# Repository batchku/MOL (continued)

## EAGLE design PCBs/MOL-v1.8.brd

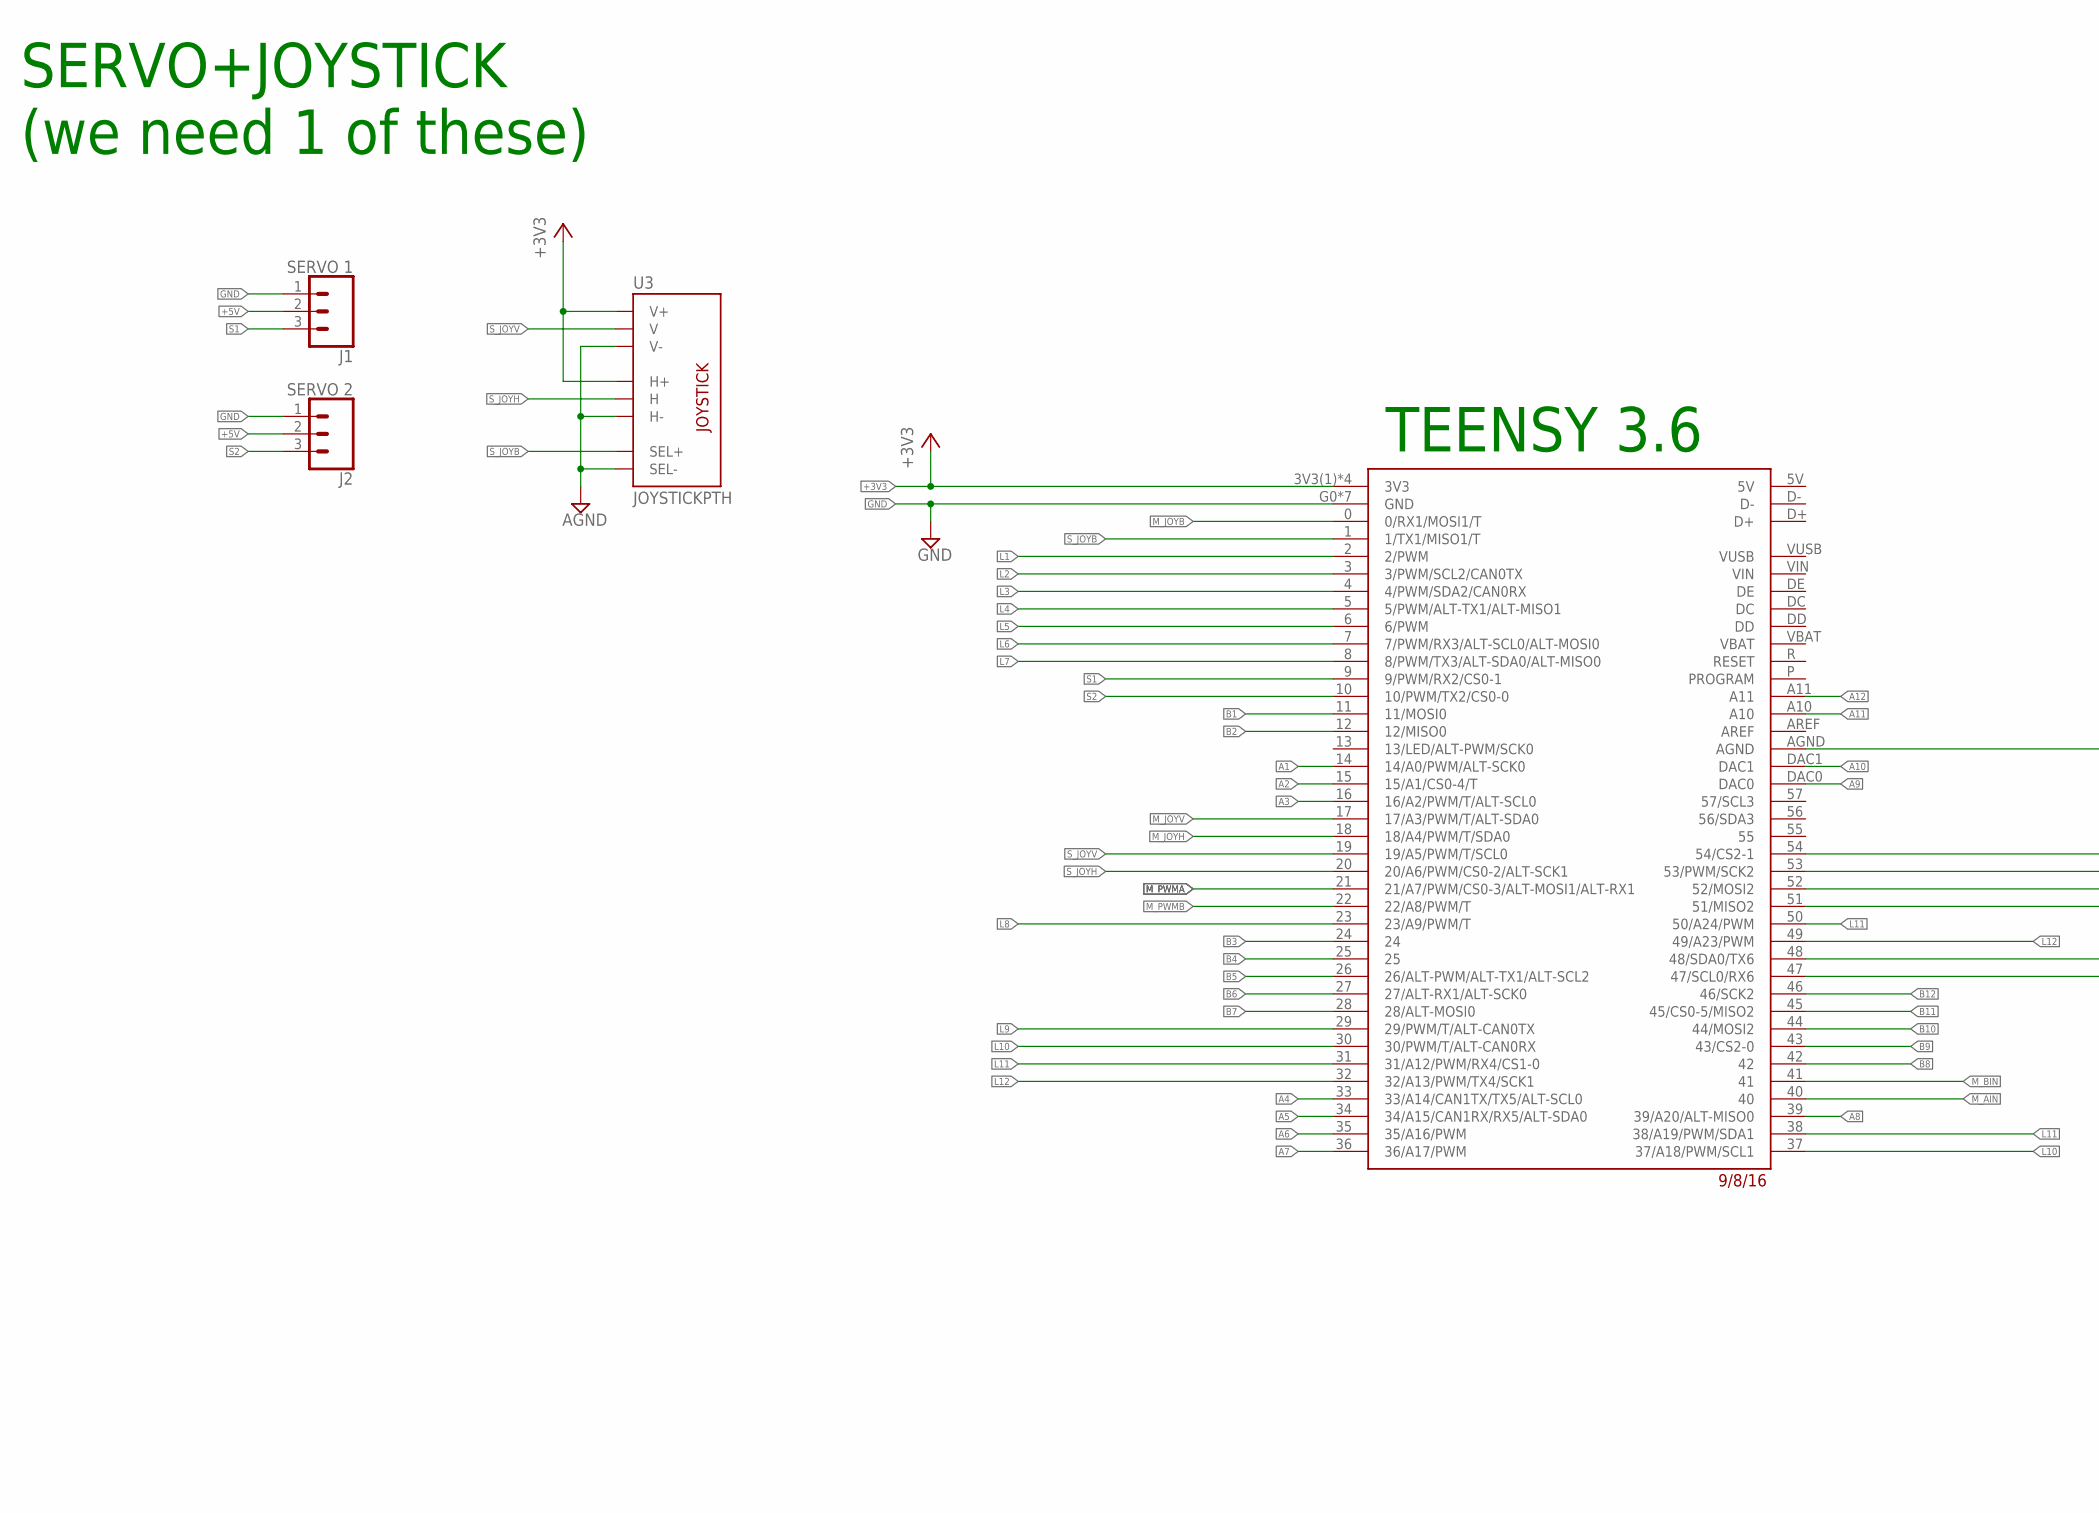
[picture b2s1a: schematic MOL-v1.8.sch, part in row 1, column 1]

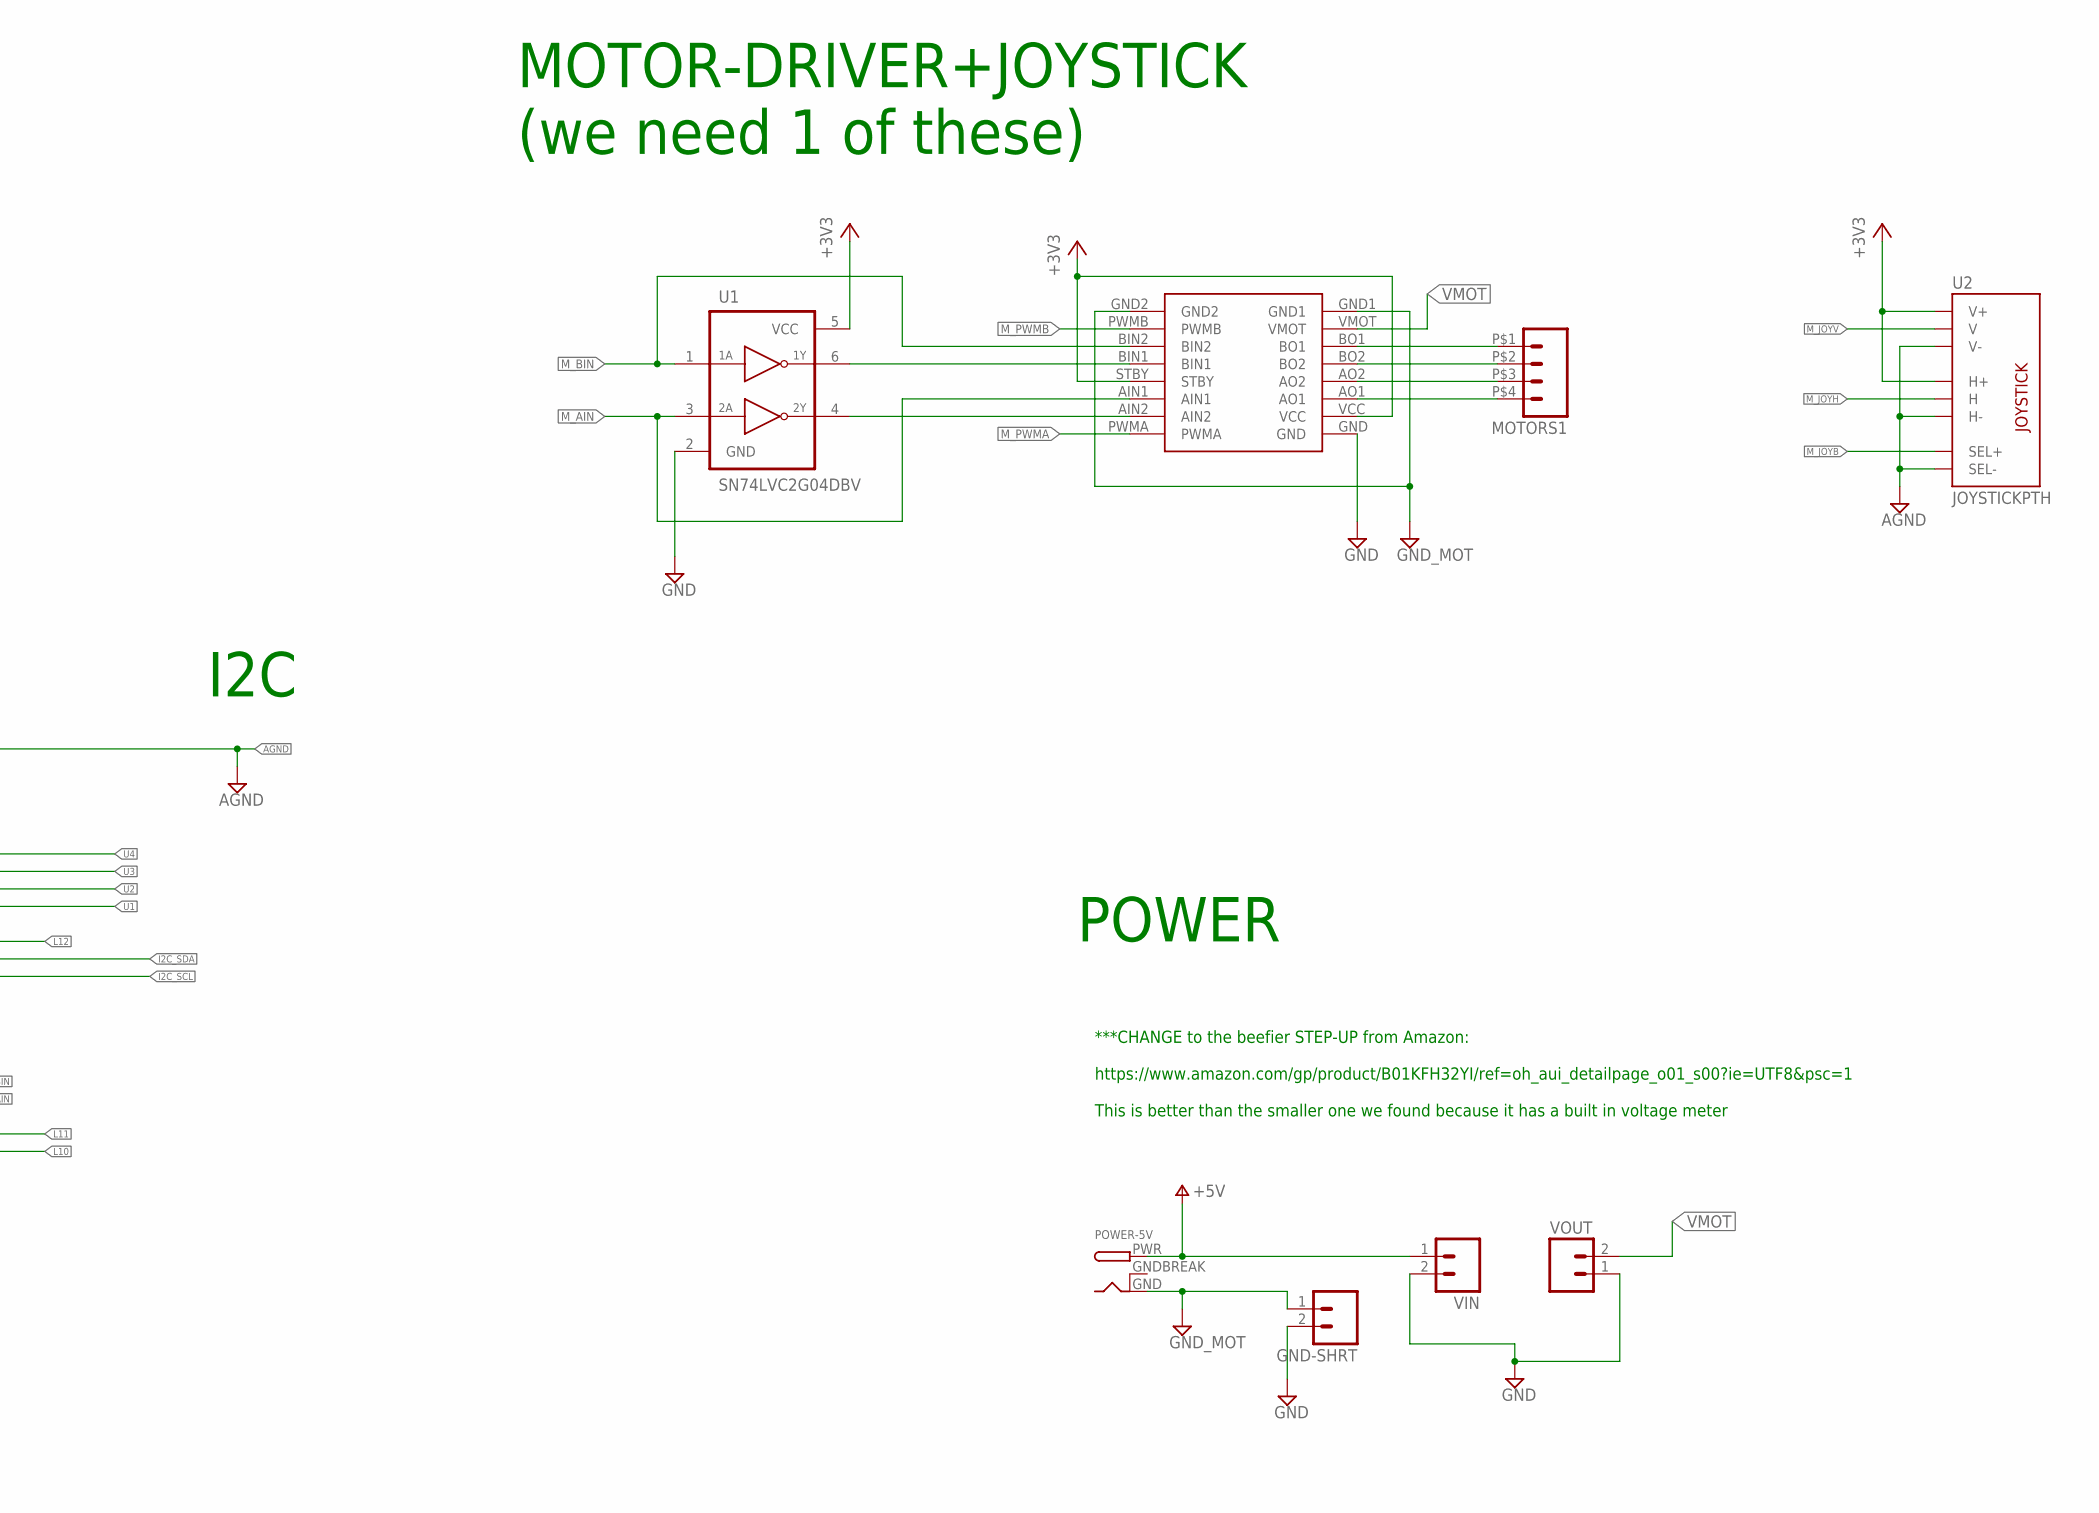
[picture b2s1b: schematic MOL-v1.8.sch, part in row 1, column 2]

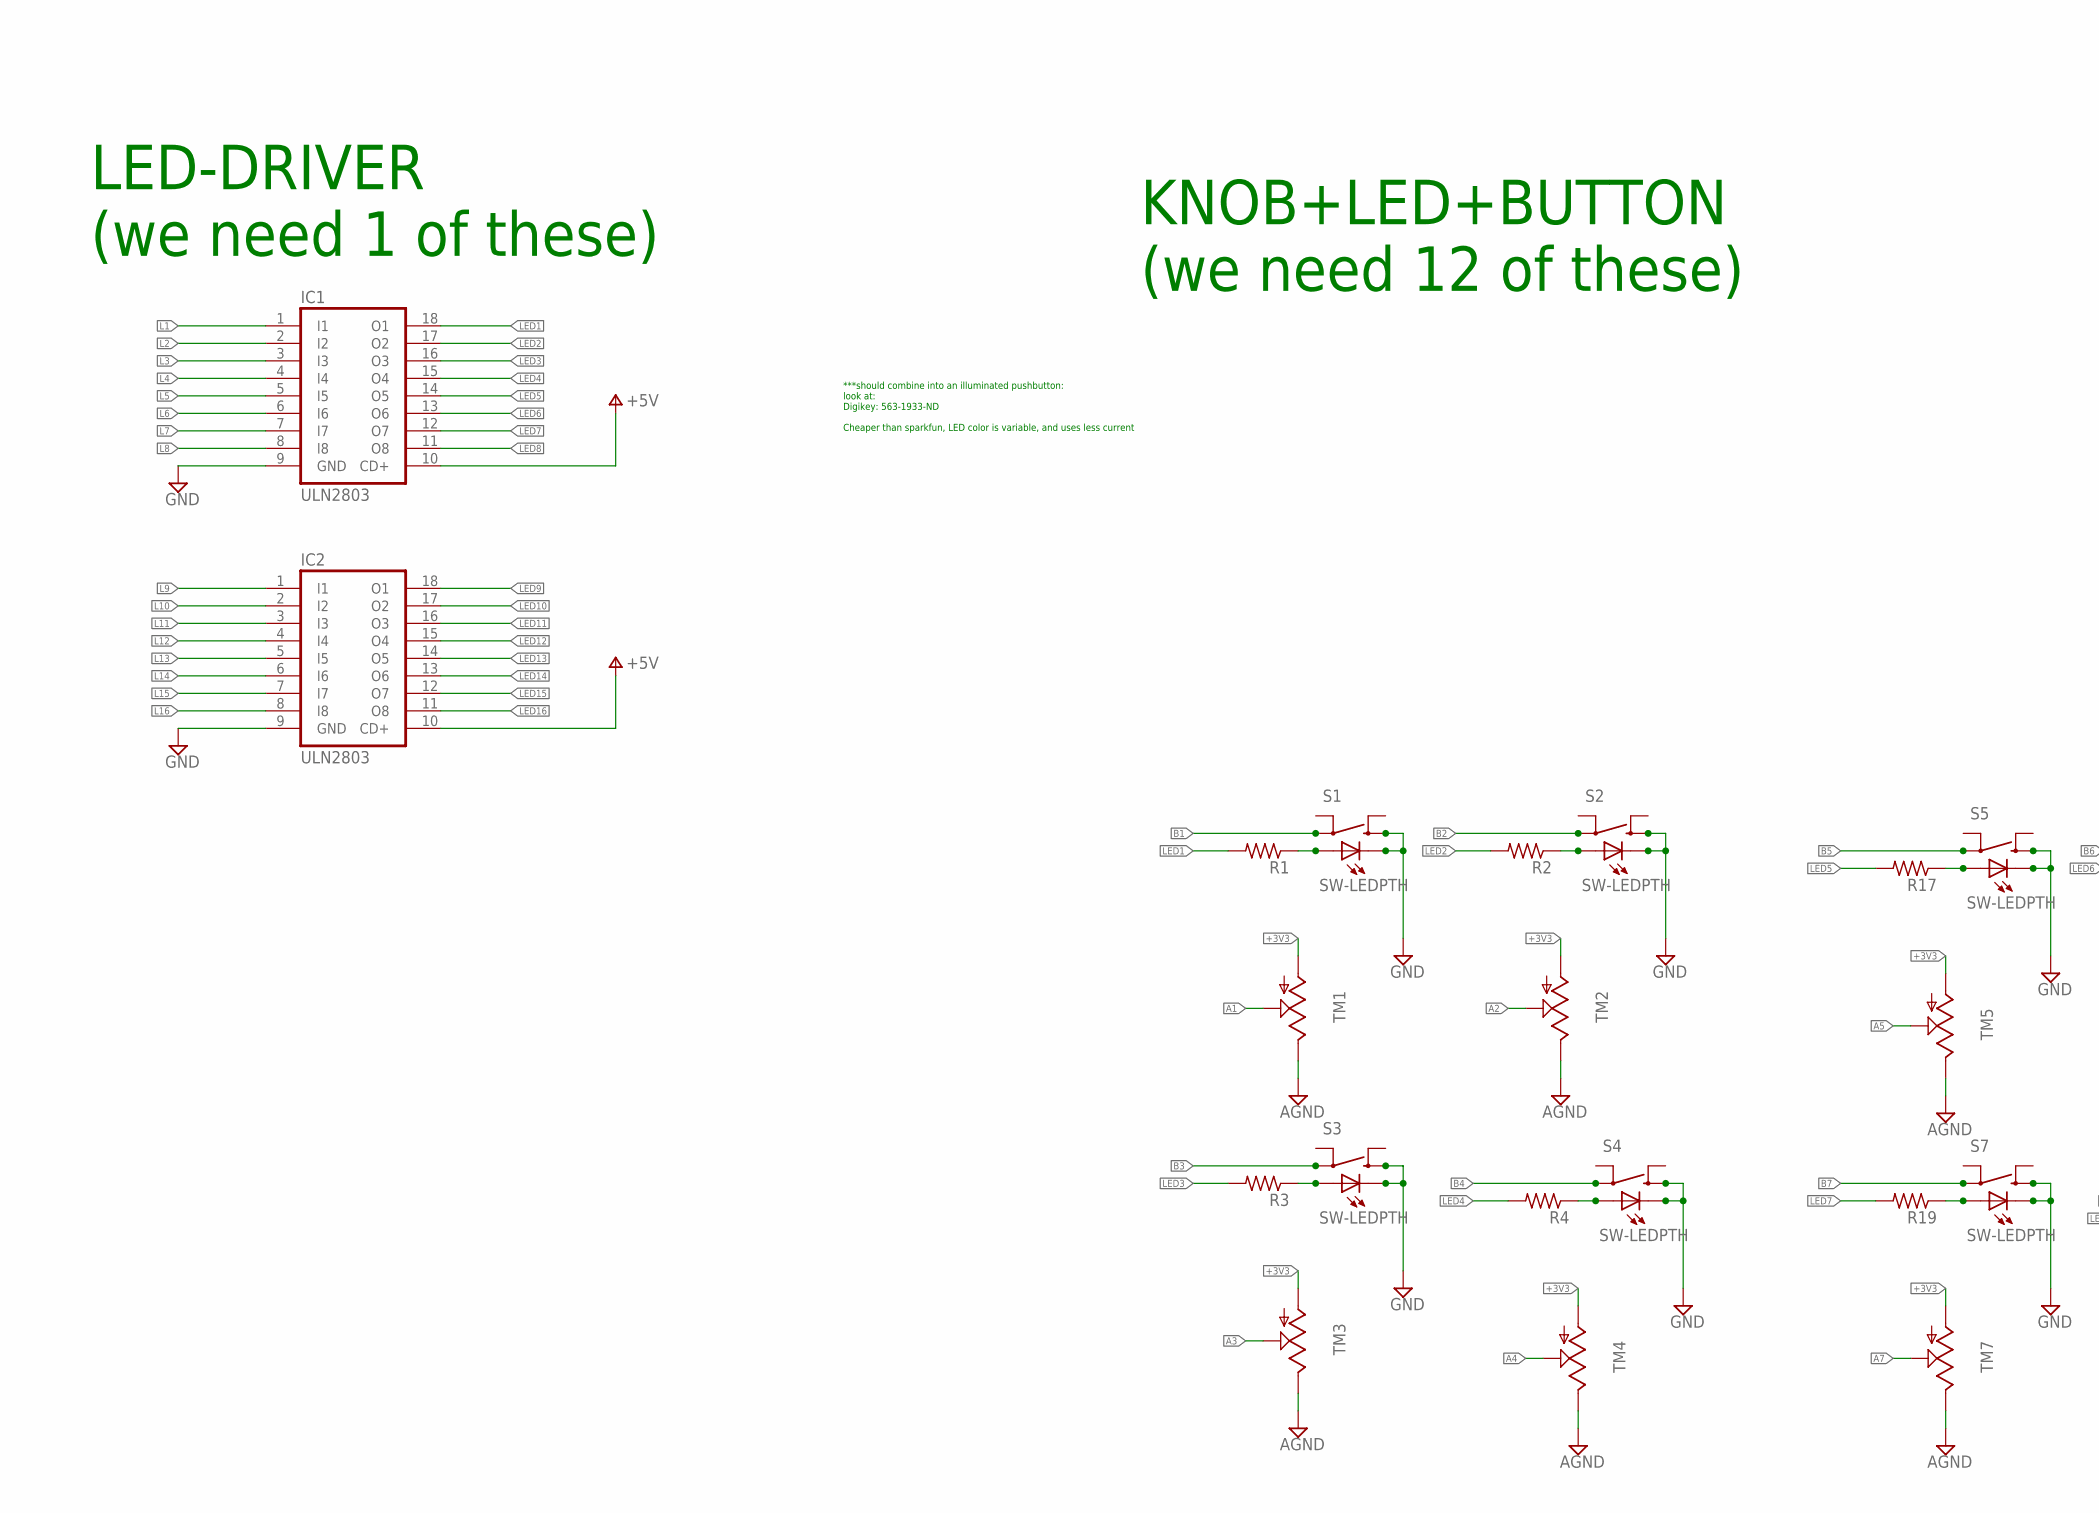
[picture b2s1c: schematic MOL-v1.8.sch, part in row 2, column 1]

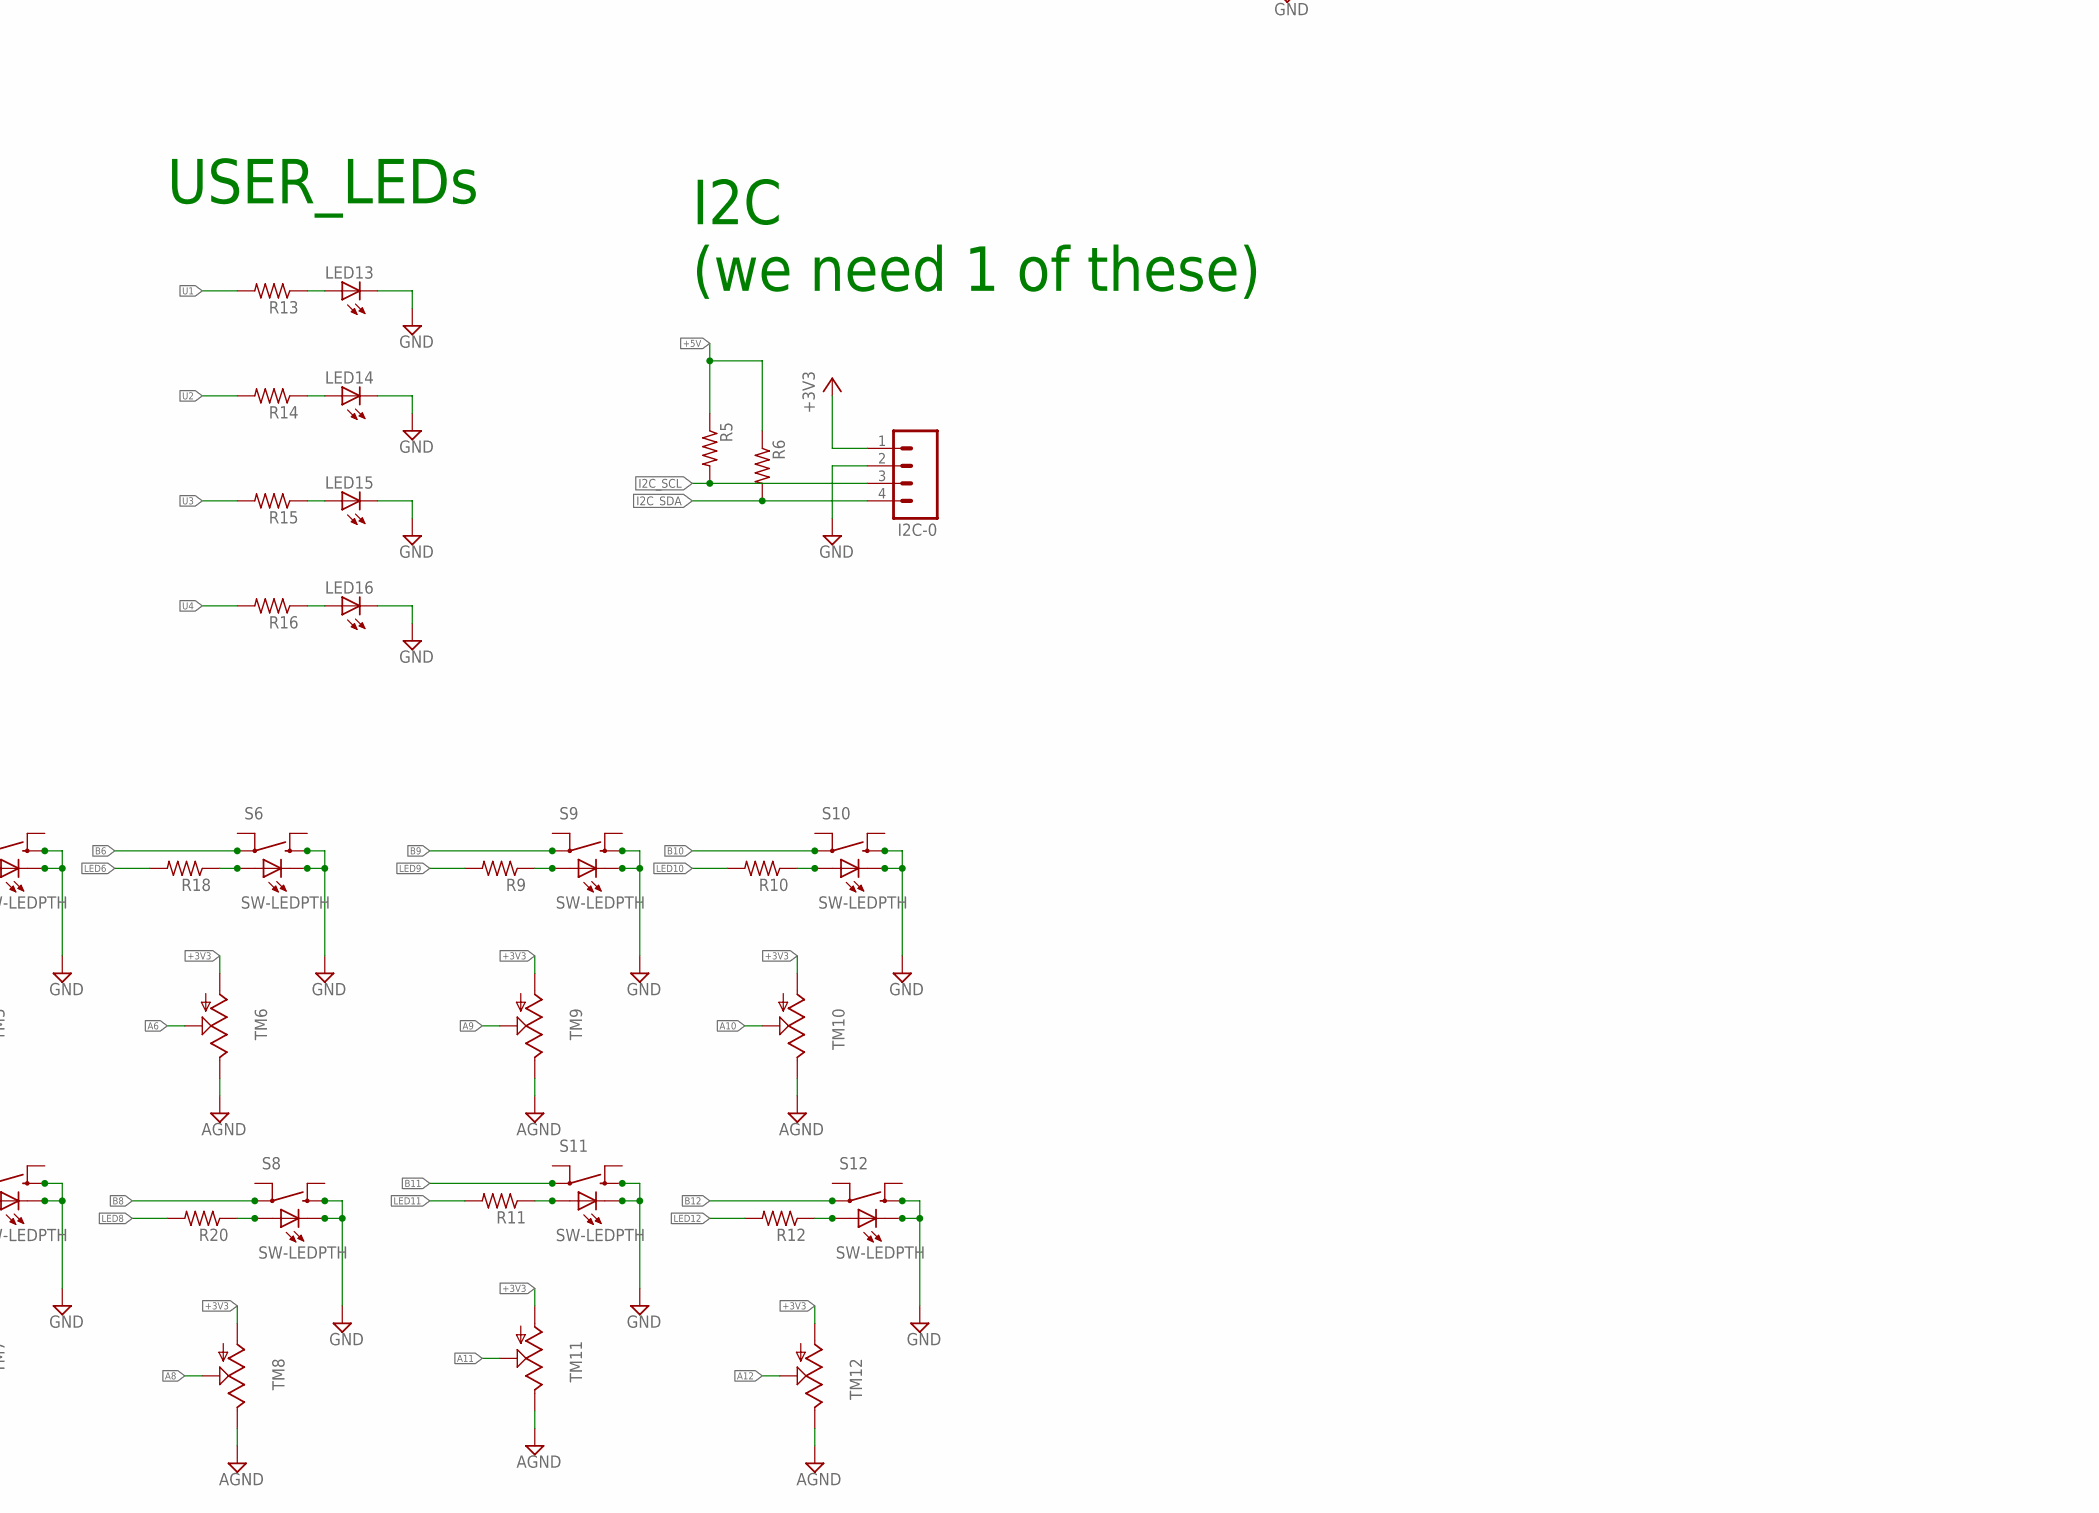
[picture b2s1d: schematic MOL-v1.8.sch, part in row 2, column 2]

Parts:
GND-SHRT: M02LOCK; 1X02_LOCK
I2C-0: M04LOCK; 1X04_LOCK
IC1, IC2: ULN2803; DIL18
J1: SERVO 1; 1X03_LOCK
J2: SERVO 2; 1X03_LOCK
LED13, LED14, LED15, LED16: LED3MM
MOTORS1: M04; SPRINGTERMINAL-2.54MM-4
POWER-5V: DCBARRELPTH; DCJACK_2MM_PTH
R1, R2, R3, R4, R5, R6, R9, R10, R11, R12, R13, R14, R15, R16, R17, R18, R19, R20: R-US_R0603; R0603
S1, S2, S3, S4, S5, S6, S7, S8, S9, S10, S11, S12: SW-LEDPTH; TR2-SWITCH-MOMENTARY-LED
TM1, TM2, TM3, TM4, TM5, TM6, TM7, TM8, TM9, TM10, TM11, TM12: TRIM; TRIM-PCB-9MM
U1: SN74LVC2G04DBV; SOT23-6
U2, U3: JOYSTICKPTH; JOYSTICK
U$1: TEENSY3_6--ALLPINS; T36
U$7: POLOLU_TB6612FNG
VIN: M02LOCK; 1X02_LOCK
VOUT: M02LOCK; 1X02_LOCK

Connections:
+3V3: I2C-0.1, TM1.1 (A), TM2.1 (A), TM3.1 (A), TM4.1 (A), TM5.1 (A), TM6.1 (A), TM7.1 (A), TM8.1 (A), TM9.1 (A), TM10.1 (A), TM11.1 (A), TM12.1 (A), U1.5 (VCC), U2.H1 (H+), U2.V1 (V+), U3.H1 (H+), U3.V1 (V+), U$1.3V3(1) (3V3), U$1.3V3(2) (3V3), U$1.3V3(3) (3V3), U$1.3V3(4) (3V3), U$7.STBY, U$7.VCC
+5V: IC1.10 (CD+), IC2.10 (CD+), J1.2, J2.2, POWER-5V.PWR, R5.1, R6.1, VIN.1
A1: TM1.2 (S), U$1.14 (14/A0/PWM/ALT-SCK0)
A2: TM2.2 (S), U$1.15 (15/A1/CS0-4/T)
A3: TM3.2 (S), U$1.16 (16/A2/PWM/T/ALT-SCL0)
A4: TM4.2 (S), U$1.33 (33/A14/CAN1TX/TX5/ALT-SCL0)
A5: TM5.2 (S), U$1.34 (34/A15/CAN1RX/RX5/ALT-SDA0)
A6: TM6.2 (S), U$1.35 (35/A16/PWM)
A7: TM7.2 (S), U$1.36 (36/A17/PWM)
A8: TM8.2 (S), U$1.39 (39/A20/ALT-MISO0)
A9: TM9.2 (S), U$1.DAC0
A10: TM10.2 (S), U$1.DAC1
A11: TM11.2 (S), U$1.A10
A12: TM12.2 (S), U$1.A11
AGND: TM1.3 (E), TM2.3 (E), TM3.3 (E), TM4.3 (E), TM5.3 (E), TM6.3 (E), TM7.3 (E), TM8.3 (E), TM9.3 (E), TM10.3 (E), TM11.3 (E), TM12.3 (E), U2.B2A (SEL-), U2.H3 (H-), U2.V3 (V-), U3.B2A (SEL-), U3.H3 (H-), U3.V3 (V-), U$1.AGND
B1: S1.3, U$1.11 (11/MOSI0)
B2: S2.3, U$1.12 (12/MISO0)
B3: S3.3, U$1.24
B4: S4.3, U$1.25
B5: S5.3, U$1.26 (26/ALT-PWM/ALT-TX1/ALT-SCL2)
B6: S6.3, U$1.27 (27/ALT-RX1/ALT-SCK0)
B7: S7.3, U$1.28 (28/ALT-MOSI0)
B8: S8.3, U$1.42
B9: S9.3, U$1.43 (43/CS2-0)
B10: S10.3, U$1.44 (44/MOSI2)
B11: S11.3, U$1.45 (45/CS0-5/MISO2)
B12: S12.3, U$1.46 (46/SCK2)
GND: GND-SHRT.2, I2C-0.2, IC1.9 (GND), IC2.9 (GND), J1.1, J2.1, LED13.K (C), LED14.K (C), LED15.K (C), LED16.K (C), S1.1, S1.C, S2.1, S2.C, S3.1, S3.C, S4.1, S4.C, S5.1, S5.C, S6.1, S6.C, S7.1, S7.C, S8.1, S8.C, S9.1, S9.C, S10.1, S10.C, S11.1, S11.C, S12.1, S12.C, U1.2 (GND), U$1.G0 (GND), U$1.G1 (GND), U$1.G2 (GND), U$1.G3 (GND), U$1.G4 (GND), U$1.G5 (GND), U$1.G6 (GND), U$7.GND, VIN.2, VOUT.1
GNDBREAK: POWER-5V.GNDBREAK
GND_MOT: GND-SHRT.1, POWER-5V.GND, U$7.GND1, U$7.GND2
I2C_SCL: I2C-0.3, R5.2, U$1.47 (47/SCL0/RX6)
I2C_SDA: I2C-0.4, R6.2, U$1.48 (48/SDA0/TX6)
L1: IC1.1 (I1), U$1.2 (2/PWM)
L2: IC1.2 (I2), U$1.3 (3/PWM/SCL2/CAN0TX)
L3: IC1.3 (I3), U$1.4 (4/PWM/SDA2/CAN0RX)
L4: IC1.4 (I4), U$1.5 (5/PWM/ALT-TX1/ALT-MISO1)
L5: IC1.5 (I5), U$1.6 (6/PWM)
L6: IC1.6 (I6), U$1.7 (7/PWM/RX3/ALT-SCL0/ALT-MOSI0)
L7: IC1.7 (I7), U$1.8 (8/PWM/TX3/ALT-SDA0/ALT-MISO0)
L8: IC1.8 (I8), U$1.23 (23/A9/PWM/T)
L9: IC2.1 (I1), U$1.29 (29/PWM/T/ALT-CAN0TX)
L10: IC2.2 (I2), U$1.30 (30/PWM/T/ALT-CAN0RX), U$1.37 (37/A18/PWM/SCL1)
L11: IC2.3 (I3), U$1.31 (31/A12/PWM/RX4/CS1-0), U$1.38 (38/A19/PWM/SDA1), U$1.50 (50/A24/PWM)
L12: IC2.4 (I4), U$1.32 (32/A13/PWM/TX4/SCK1), U$1.49 (49/A23/PWM)
L13: IC2.5 (I5)
L14: IC2.6 (I6)
L15: IC2.7 (I7)
L16: IC2.8 (I8)
LED1: IC1.18 (O1), R1.2
LED2: IC1.17 (O2), R2.2
LED3: IC1.16 (O3), R3.2
LED4: IC1.15 (O4), R4.2
LED5: IC1.14 (O5), R17.2
LED6: IC1.13 (O6), R18.2
LED7: IC1.12 (O7), R19.2
LED8: IC1.11 (O8), R20.2
LED9: IC2.18 (O1), R9.2
LED10: IC2.17 (O2), R10.2
LED11: IC2.16 (O3), R11.2
LED12: IC2.15 (O4), R12.2
LED13: IC2.14 (O5)
LED14: IC2.13 (O6)
LED15: IC2.12 (O7)
LED16: IC2.11 (O8)
M_AIN: U1.3 (2A), U$1.40, U$7.AIN1
M_BIN: U1.1 (1A), U$1.41, U$7.BIN2
M_JOYB: U2.B1A (SEL+), U$1.0 (0/RX1/MOSI1/T)
M_JOYH: U2.H2 (H), U$1.18 (18/A4/PWM/T/SDA0)
M_JOYV: U2.V2 (V), U$1.17 (17/A3/PWM/T/ALT-SDA0)
M_PWMA: U$1.21 (21/A7/PWM/CS0-3/ALT-MOSI1/ALT-RX1), U$7.PWMA
M_PWMB: U$1.22 (22/A8/PWM/T), U$7.PWMB
unnamed: R1.1, S1.A
unnamed: LED13.A, R13.1
unnamed: LED14.A, R14.1
unnamed: LED15.A, R15.1
unnamed: U1.6 (1Y), U$7.BIN1
unnamed: U1.4 (2Y), U$7.AIN2
unnamed: LED16.A, R16.1
unnamed: R2.1, S2.A
unnamed: R3.1, S3.A
unnamed: R4.1, S4.A
unnamed: R9.1, S9.A
unnamed: R10.1, S10.A
unnamed: R11.1, S11.A
unnamed: R12.1, S12.A
unnamed: R17.1, S5.A
unnamed: R18.1, S6.A
unnamed: R19.1, S7.A
unnamed: R20.1, S8.A
unnamed: MOTORS1.P$1 (1), U$7.BO1
unnamed: MOTORS1.P$2 (2), U$7.BO2
unnamed: MOTORS1.P$3 (3), U$7.AO2
unnamed: MOTORS1.P$4 (4), U$7.AO1
S1: J1.3, U$1.9 (9/PWM/RX2/CS0-1)
S2: J2.3, U$1.10 (10/PWM/TX2/CS0-0)
S_JOYB: U3.B1A (SEL+), U$1.1 (1/TX1/MISO1/T)
S_JOYH: U3.H2 (H), U$1.20 (20/A6/PWM/CS0-2/ALT-SCK1)
S_JOYV: U3.V2 (V), U$1.19 (19/A5/PWM/T/SCL0)
U1: R13.2, U$1.51 (51/MISO2)
U2: R14.2, U$1.52 (52/MOSI2)
U3: R15.2, U$1.53 (53/PWM/SCK2)
U4: R16.2, U$1.54 (54/CS2-1)
VMOT: U$7.VMOT, VOUT.2

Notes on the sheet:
***should combine into an illuminated pushbutton: look at: Digikey: 563-1933-ND Cheaper than sparkfun, LED color is variable, and uses less current
KNOB+LED+BUTTON (we need 12 of these)
MOTOR-DRIVER+JOYSTICK (we need 1 of these)
***CHANGE to the beefier STEP-UP from Amazon: https://www.amazon.com/gp/product/B01KFH32YI/ref=oh_aui_detailpage_o01_s00?ie=UTF8&psc=1 This is better than the smaller one we found because it has a built in voltage meter
POWER
SERVO+JOYSTICK (we need 1 of these)
LED-DRIVER (we need 1 of these)
USER_LEDs
I2C (we need 1 of these)
I2C
TEENSY 3.6

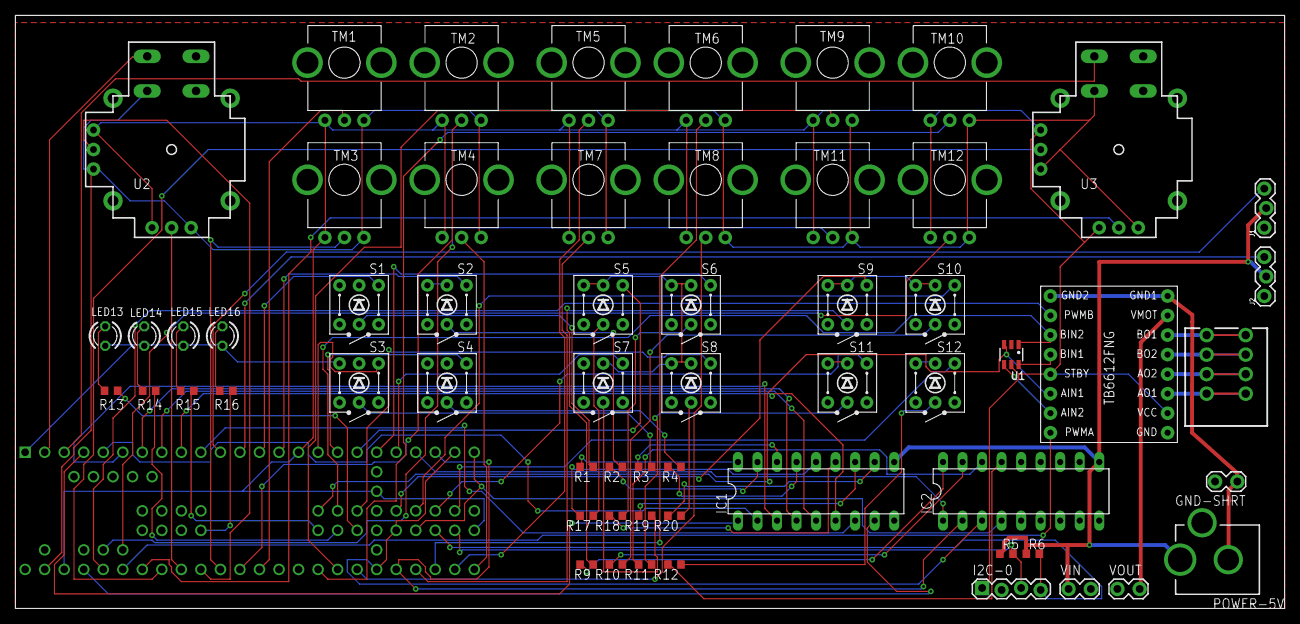
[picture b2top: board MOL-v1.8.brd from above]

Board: 2 copper layers, 165.1 x 77.1 mm, 61 parts (1 on the bottom side), 94 nets.

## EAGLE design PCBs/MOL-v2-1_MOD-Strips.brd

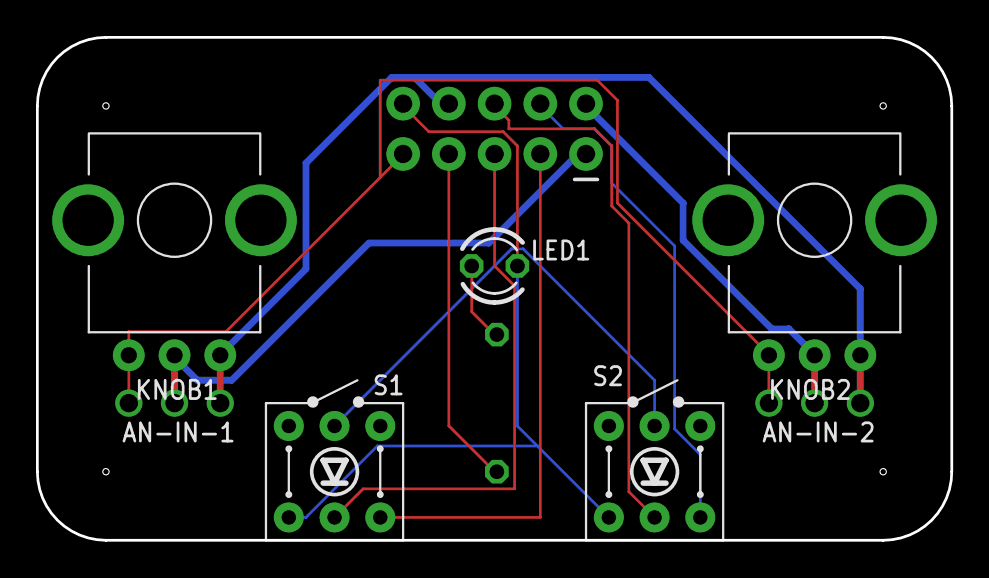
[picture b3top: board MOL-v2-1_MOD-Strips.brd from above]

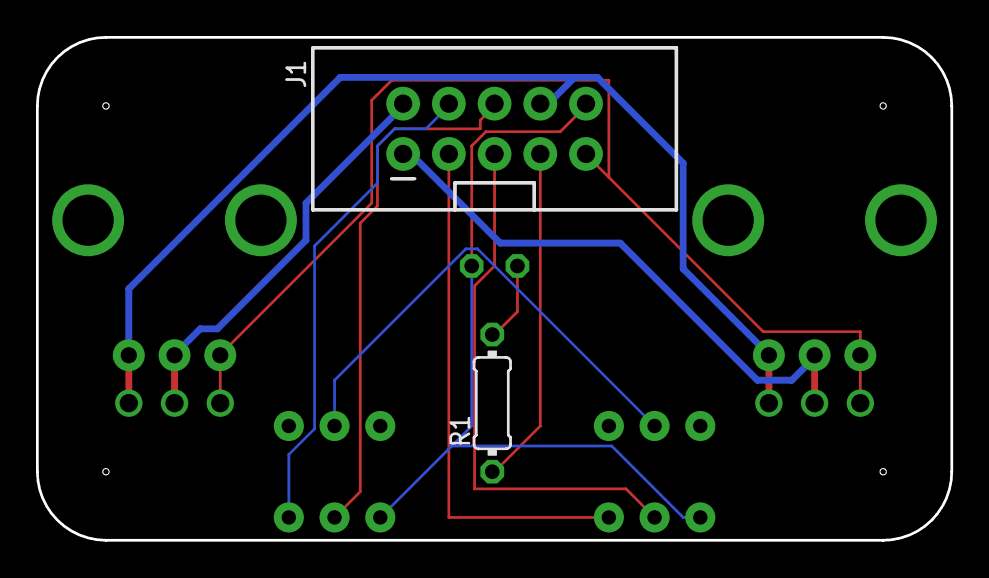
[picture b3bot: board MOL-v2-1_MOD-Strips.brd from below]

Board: 2 copper layers, 50.8 x 27.9 mm, 9 parts (2 on the bottom side), 12 nets.

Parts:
AN-IN-1, AN-IN-2: 1X03_NO_SILK
J1: 2X5-SHROUDED_LOCK
KNOB1, KNOB2: TRIM-PCB-9MM
LED1: LED3MM
R1: 220; 0204/7
S1, S2: SW-LEDPTH; TR2-SWITCH-MOMENTARY-LED

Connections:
+3V3: AN-IN-1.1, AN-IN-2.1, J1.9, KNOB1.1, KNOB2.1
AGND: AN-IN-1.3, AN-IN-2.3, J1.8, KNOB1.3, KNOB2.3
AN1: AN-IN-1.2, J1.1, KNOB1.2
AN2: AN-IN-2.2, J1.2, KNOB2.2
B1: J1.3, S1.1
B2: J1.4, S2.1
GND: J1.10, LED1.K, S1.3, S2.3
LED1: J1.7, R1.1
N1: LED1.A, R1.2
PWM_1: J1.5, S1.C
PWM_2: J1.6, S2.C
V+: S1.A, S2.A

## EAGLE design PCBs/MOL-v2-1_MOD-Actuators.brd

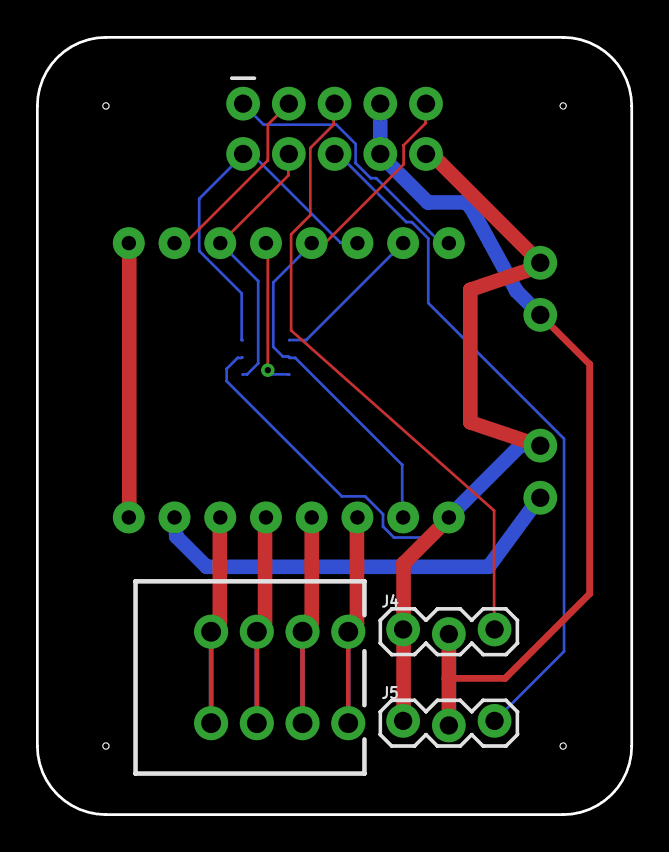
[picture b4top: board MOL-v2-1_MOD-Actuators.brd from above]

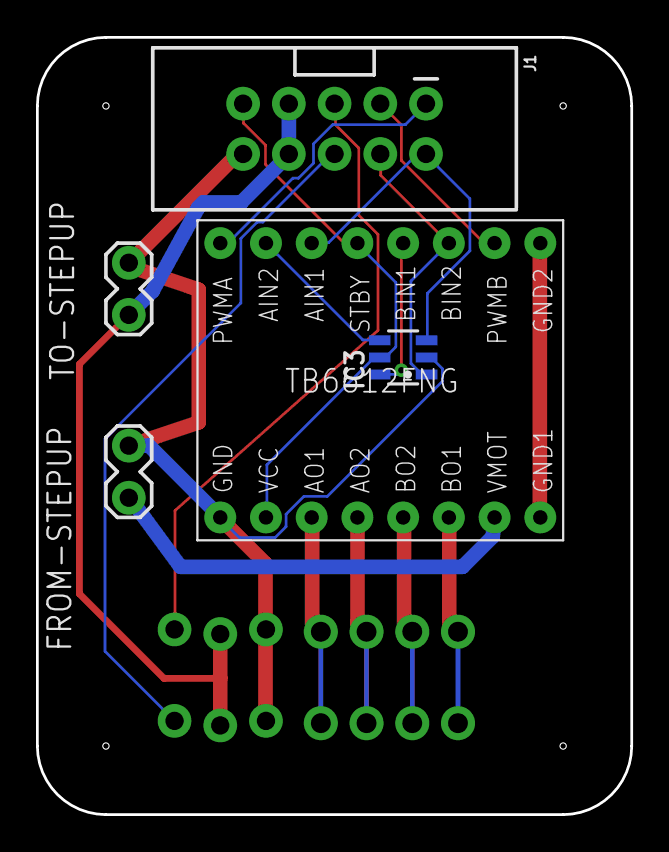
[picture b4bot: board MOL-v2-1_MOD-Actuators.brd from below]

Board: 2 copper layers, 33.0 x 43.2 mm, 8 parts (5 on the bottom side), 17 nets.

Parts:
FROM-STEPUP: 1X02_LOCK
IC3: SN74LVC2G04DBV; SOT23-6
J1: ACTUATORS; 2X5-SHROUDED_LOCK
J4: SERVO 1; 1X03_LOCK@1
J5: SERVO 2; 1X03_LOCK@1
MOTORS1: SPRINGTERMINAL-2.54MM-4
TO-STEPUP: 1X02_LOCK
U$7: POLOLU_TB6612FNG

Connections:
+3V3: IC3.5, J1.9, U$7.STBY, U$7.VCC
+5V: J1.7, J1.8, J4.2, J5.2, TO-STEPUP.1
GND: FROM-STEPUP.1, IC3.2, J1.10, J4.1, J5.1, TO-STEPUP.2, U$7.GND
GND_MOT: U$7.GND1, U$7.GND2
M_AIN: IC3.3, J1.2, U$7.AIN1
M_BIN: IC3.1, J1.4, U$7.BIN2
M_PWMA: J1.1, U$7.PWMA
M_PWMB: J1.3, U$7.PWMB
unnamed: MOTORS1.P$1, U$7.AO1
unnamed: MOTORS1.P$2, U$7.AO2
unnamed: MOTORS1.P$3, U$7.BO2
unnamed: MOTORS1.P$4, U$7.BO1
unnamed: IC3.6, U$7.BIN1
unnamed: IC3.4, U$7.AIN2
S1: J1.5, J4.3
S2: J1.6, J5.3
VMOT: FROM-STEPUP.2, U$7.VMOT
